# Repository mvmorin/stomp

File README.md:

# Stomp
Split, staggered column 40% keyboard. Designed in KiCad with symbols and footprints from [keyboard-parts](https://github.com/mvmorin/keyboard-parts) library.

# Features
* Low profile and flat-bottom design to be put on top of laptop keyboards.
* Extra large stagger for pinky columns.
* Based on a standard 40% 4x12 layout but only contains the reachable keys. It should be compatible with most 40% 4x12 layouts.
* Only a single Teensy or Pro-Micro-compatible controller board needed.
* Full FR4 (PCB) design, including backplate, for easy single order manufacturing.
* Both MX and Alps plates.

# PCB and Plate files
The production files for the latest version can be found in the 'gerber' directory. They have been test printed at [JLCPCB](https://jlcpcb.com/). Any notes from the test prints can be found below.

## Test Print Comments
The mounting pin holes for 5-pin MX-switches are bit tighter than I would have preferred. They are perfectly usable with the Ink Blacks I tested them but they will be enlarged in any potential future revisions.

# Licenses

This project is released under the [Creative Commons CC-BY-SA 4.0](https://creativecommons.org/licenses/by-sa/4.0/legalcode) license, Copyright (c) Martin Morin 2020.
Some footprints and symbols are based on parts from the [KiCad libraries](https://kicad-pcb.org/libraries/), released under the same [CC-BY-SA 4.0](https://creativecommons.org/licenses/by-sa/4.0/legalcode) license.

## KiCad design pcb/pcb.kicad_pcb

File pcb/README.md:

# Base PCB
The footprints contains all information for the plate. The switch cutouts and the plate silk-screen layer are exported via the *eco1*, *eco2*, and *cmts* layers and are then imported in the backplate PCB drawing. The board-outline/edge-cuts is imported from the *board-outline* directory.

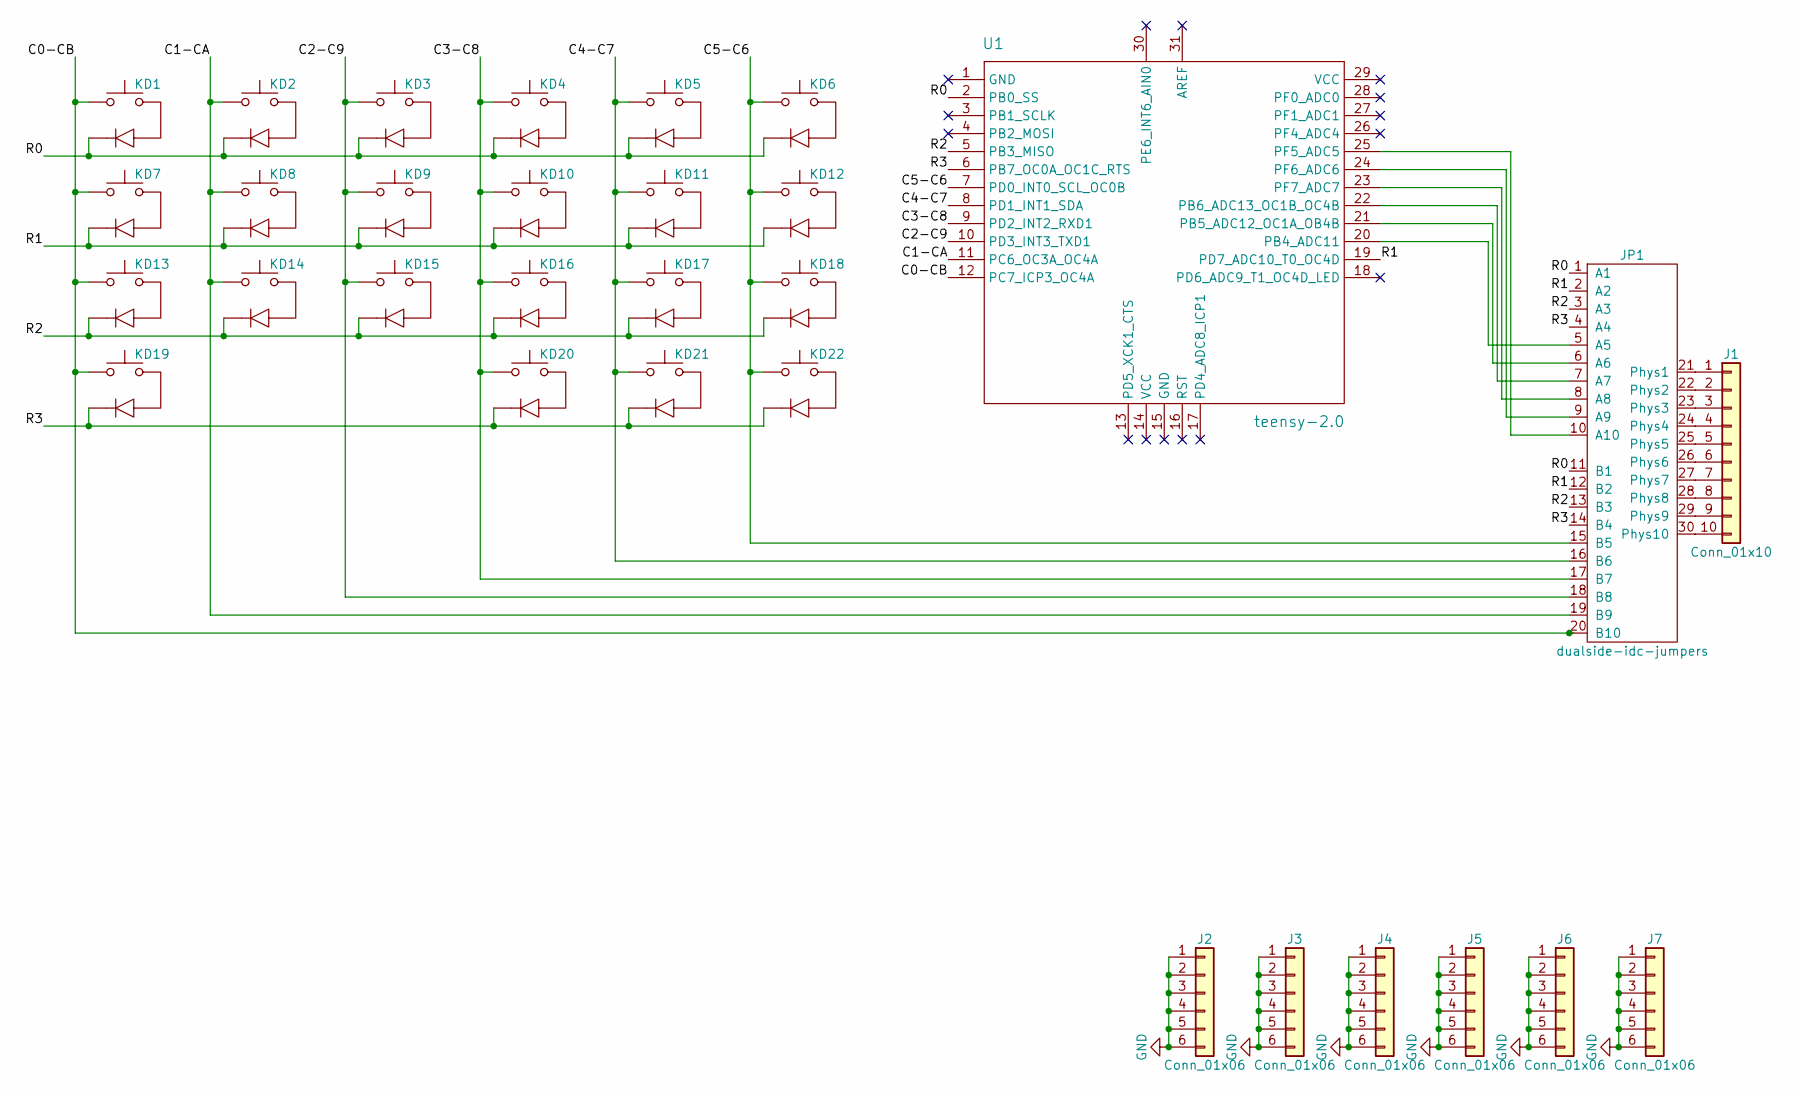
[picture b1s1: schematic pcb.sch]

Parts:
J1: Conn_01x10; idc-header-dualside_2x05_2.54mm
J2, J3, J4, J5, J6, J7: Conn_01x06; header_sym_1x06_2.54mm
JP1: dualside-idc-jumpers
KD1, KD2, KD3, KD4, KD5, KD6, KD7, KD8, KD9, KD10, KD11, KD12, KD13, KD14, KD15, KD16, KD17, KD18, KD19, KD20, KD22: switch-w-diode; mxalps_w_diode_R_100U_dualside
KD21: switch-w-diode; mxalps_w_diode_R_125U_dualside
U1: teensy-2.0; teensy2.0_dualside

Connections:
/C0-CB: JP1.20 (B10), KD1.1 (A), KD7.1 (A), KD13.1 (A), KD19.1 (A), U1.12 (PC7_ICP3_OC4A)
/C1-CA: JP1.19 (B9), KD2.1 (A), KD8.1 (A), KD14.1 (A), U1.11 (PC6_OC3A_OC4A)
/C2-C9: JP1.18 (B8), KD3.1 (A), KD9.1 (A), KD15.1 (A), U1.10 (PD3_INT3_TXD1)
/C3-C8: JP1.17 (B7), KD4.1 (A), KD10.1 (A), KD16.1 (A), KD20.1 (A), U1.9 (PD2_INT2_RXD1)
/C4-C7: JP1.16 (B6), KD5.1 (A), KD11.1 (A), KD17.1 (A), KD21.1 (A), U1.8 (PD1_INT1_SDA)
/C5-C6: JP1.15 (B5), KD6.1 (A), KD12.1 (A), KD18.1 (A), KD22.1 (A), U1.7 (PD0_INT0_SCL_OC0B)
/R0: JP1.1 (A1), JP1.11 (B1), KD1.2 (K), KD2.2 (K), KD3.2 (K), KD4.2 (K), KD5.2 (K), KD6.2 (K), U1.2 (PB0_SS)
/R1: JP1.2 (A2), JP1.12 (B2), KD7.2 (K), KD8.2 (K), KD9.2 (K), KD10.2 (K), KD11.2 (K), KD12.2 (K), U1.19 (PD7_ADC10_T0_OC4D)
/R2: JP1.3 (A3), JP1.13 (B3), KD13.2 (K), KD14.2 (K), KD15.2 (K), KD16.2 (K), KD17.2 (K), KD18.2 (K), U1.5 (PB3_MISO)
/R3: JP1.4 (A4), JP1.14 (B4), KD19.2 (K), KD20.2 (K), KD21.2 (K), KD22.2 (K), U1.6 (PB7_OC0A_OC1C_RTS)
GND: J2.1, J2.2, J2.3, J2.4, J2.5, J2.6, J3.1, J3.2, J3.3, J3.4, J3.5, J3.6, J4.1, J4.2, J4.3, J4.4, J4.5, J4.6, J5.1, J5.2, J5.3, J5.4, J5.5, J5.6, J6.1, J6.2, J6.3, J6.4, J6.5, J6.6, J7.1, J7.2, J7.3, J7.4, J7.5, J7.6
unnamed: J1.1, JP1.21 (Phys1)
unnamed: J1.2, JP1.22 (Phys2)
unnamed: J1.3, JP1.23 (Phys3)
unnamed: J1.4, JP1.24 (Phys4)
unnamed: J1.5, JP1.25 (Phys5)
unnamed: J1.6, JP1.26 (Phys6)
unnamed: J1.7, JP1.27 (Phys7)
unnamed: J1.8, JP1.28 (Phys8)
unnamed: J1.9, JP1.29 (Phys9)
unnamed: J1.10, JP1.30 (Phys10)
unnamed: JP1.5 (A5), U1.20 (PB4_ADC11)
unnamed: JP1.6 (A6), U1.21 (PB5_ADC12_OC1A_OB4B)
unnamed: JP1.7 (A7), U1.22 (PB6_ADC13_OC1B_OC4B)
unnamed: JP1.8 (A8), U1.23 (PF7_ADC7)
unnamed: JP1.9 (A9), U1.24 (PF6_ADC6)
unnamed: JP1.10 (A10), U1.25 (PF5_ADC5)

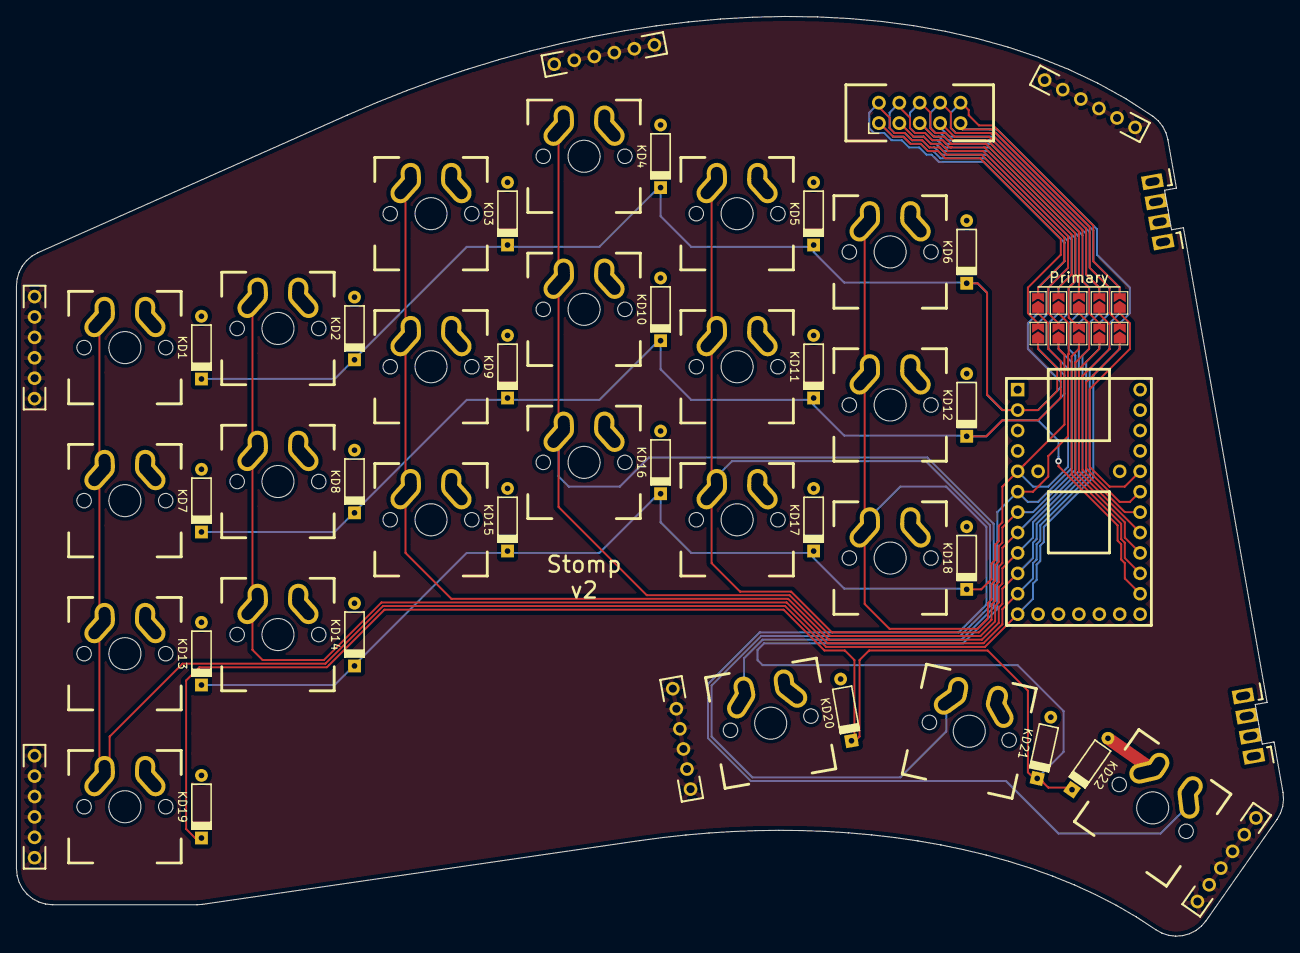
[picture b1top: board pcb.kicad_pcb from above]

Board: 2 copper layers, 157.7 x 114.5 mm, 31 parts (1 on the bottom side), 27 nets.

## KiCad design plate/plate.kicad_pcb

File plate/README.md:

# Plates
The switch cutouts and the plate silk-screen are imported from the base PCB drawing. The edge-cuts are imported from the *board-outline* directory.

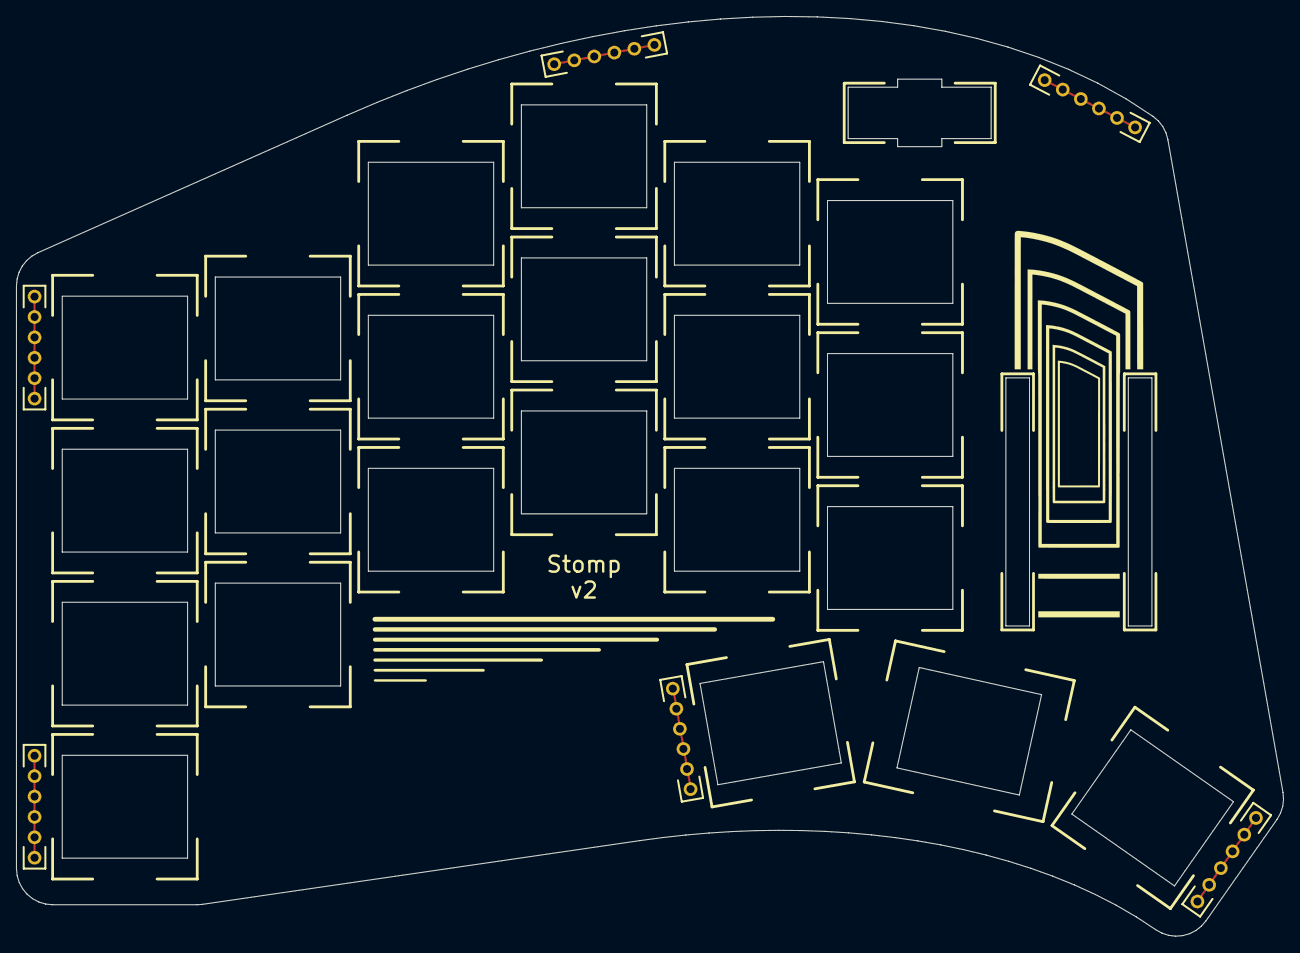
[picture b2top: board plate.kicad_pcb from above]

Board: 2 copper layers, 157.7 x 114.5 mm, 6 parts (0 on the bottom side), 6 nets.

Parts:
J1, J2, J3, J4, J5, J6: Conn_01x06; header_sym_1x06_2.54mm

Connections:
unnamed: J1.1, J1.2, J1.3, J1.4, J1.5, J1.6
unnamed: J2.1, J2.2, J2.3, J2.4, J2.5, J2.6
unnamed: J3.1, J3.2, J3.3, J3.4, J3.5, J3.6
unnamed: J4.1, J4.2, J4.3, J4.4, J4.5, J4.6
unnamed: J5.1, J5.2, J5.3, J5.4, J5.5, J5.6
unnamed: J6.1, J6.2, J6.3, J6.4, J6.5, J6.6

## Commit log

2020-06-16 Squashed 'keyboard-parts/' content from commit 7592995
    git-subtree-dir: keyboard-parts
    git-subtree-split: 75929951316423486571924b044501165a41824c
2020-06-16 Copy over basic structure from touchmark
2020-06-16 Add new double sided parts
2020-06-16 Create schematic and start on board
2020-06-21 Add/remove teensy and header footprints for dualsided keyboards
2020-06-21 Final routing of base pcb. Outline left.
2020-06-21 Finish base pcb, decorations left
2020-06-25 Add/update double sided footprints
2020-06-25 Add headers for board interconnect
2020-06-25 Rotate header to avoid twisting ribbon cable
2020-06-26 Fatter silk and tighter headers cutouts in teensy and IDC
2020-06-26 Add 1x6 header and fix reference in teensy
2020-06-26 Update board outline
2020-06-26 Add logos to main pcb
2020-06-27 Add plate
2020-06-27 Update component 3d models
2020-06-27 Remove arcs on silk
    JLCPCB's gerber viewer draws arcs reversed, might not be a real problem
    but why bother
2020-06-27 Add gerbers
2020-07-13 Fix minor silk-screen misses and alignment
2020-07-14 Change board outline
2020-07-14 Fix one header
2020-07-16 Finish refinement of board outline
2020-07-16 Change pin for column B to avoid teensy LED
2020-07-16 Slight reposition and reroute of inter-pcb-header
2020-09-03 Use single IDC header and prep outline for magnets
2020-09-11 Add higher resolution outline curves and magnet supports
2020-11-12 Add two row teensy footprint for mcu-dummy
2020-11-12 Add mcu-dummy for secondary side and new logos on plate
2020-11-13 Change line widths of graphics to balance the look better
2020-11-16 Update version number to v2 and add new gerbers
2020-11-28 Squashed 'keyboard-parts/' changes from 7592995..d7591ea
    d7591ea Update README.md
    9f18485 Add two row teensy footprint for mcu-dummy
    8ce1f52 Add higher resolution outline curves and magnet supports
    7473e23 Use single IDC header and prep outline for magnets
    80d8032 Update component 3d models
    6c1f2c6 Add 1x6 header and fix reference in teensy
2020-11-28 Enlarge pin-holes for 5-pin MX switches
